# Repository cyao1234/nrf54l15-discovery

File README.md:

# nRF54L15 Discovery

The nRF54L15 Discovery board is a development kit designed around the nRF54L15 and nRF52820 multiprotocol Bluetooth low-power SoCs. In the normal configuration, the nRF52820 is used as an interface CMSIS-DAP MCU, enabling onboard debugging and programming, eliminating the need for external debuggers. The Interface MCU interfaces with the host via USB and exposes an SWD and UART bridge for development usage.

Both MCUs are connected via two mousebite bridges, which can be snapped in two, allowing both chips to be used separately. Both boards have standalone voltage regulators and have their own USB-C power supply connector.

The processors are paired with an nPM1300 PMIC that supports LiPo charging and a TPS63900 high-efficiency, low Iq buck-boost converter. Both voltage regulators can be configured for 1.8V or 3.3V, enabling a flexible operating voltage domain. The nPM1300 also negotiates USB-C PD with your charger and dynamically changes the battery charging rate.

It also has USB-C, LEDs, Buttons, and U.FL receptacles for a 2.4 GHz Antenna and a 13.56 MHz NFC Antenna. The SWD and UART headers are exposed via I/O pins.

### Key Features
- Nordic Semiconductor [nRF54L15](https://www.nordicsemi.com/Products/nRF54L15) SoC
    - 128 MHz Arm Cortex®-M33 processor and 128 MHz RISC-V coprocessor 
    - 1.5 MB NVM and 256 KB RAM
    - Multiprotocol 2.4 GHz radio supporting Bluetooth Low Energy, 802.15.4-2020, and 2.4 GHz proprietary modes (up to 4 Mbps)
    - Advanced security features with physical protection
    - Global RTC (GRTC) available in System OFF mode
    - 5x SPI/UART/I2C, 3x PWM, 2x QDEC, I2S, PDM, 14-bit ADC, GPIOs
    - Integrated NFC-A Tag
    - 0.7 μA to 2.9 μA sleep mode power consumption
    - U.FL NFC connector
- Nordic Semiconductor [nRF52820](https://www.nordicsemi.com/Products/nRF52820) SoC
    - 64 MHz Arm Cortex®-M4
    - 256 KB Flash and 32 KB RAM
    - Full Speed USB 2.0
    - Bluetooth Low Energy multiprotocol
    - U.FL 2.4GHz NFC Antenna
- [nPM1300](https://www.nordicsemi.com/Products/nPM1300) 500 nA PMIC with integrated 32-800mA LiPo battery charger
    - 200 mA buck-boost converter with 93% efficiency
    - 50 mA switchable LDO for LEDs (turn off for 0 current leakage)
    - 1.0-3.3V variable voltage configurable in 100 mV steps
    - 32-800 mA LiPo battery charger with power path
    - USB Type-C compliant with 100 mA, 500 mA, and 1500 mA current limit
- Up to 48 GPIOs (29 for nRF54L15, 15 for nRF52820, 2 for nPM1300)
- Shipped with CMSIS-DAP pre-flashed on the nRF52820, ready for direct use
- ARM Serial Wire Debug (SWD) port via edge pins and 3-pin header
- TPS63900 75 nA buck-boost converter with 1.8V/3.3V configurable power supply for I/Os
- USB-C, user LED and buttons
- Dual-row 40+20 pins in 91x21mm form factor with castellated edges
- Snappable into 2 individual devboards, all capable of standalone operations
- Supports Zephyr, nRF Connect SDK, Python, etc.

### Hardware Diagram

The hardware design files are also available on [GitHub](https://github.com/cheyao/nrf54l15-discovery/), licensed under the CERN OHL V2.

### Programming guide

The board is programmable out of the box. Just run `west flash -r pyocd` to flash the board.

To get started, just follow Zephyr's [Getting Started](https://docs.zephyrproject.org/latest/develop/getting_started/index.html) guide. Everything is the same, except replace `<your-board-name>` with `nrf54l15_discovery/nrf54l15/cpuapp/s` (or without the `/ns` for secure version).

### Where to Buy

The nRF54L15 Discovery is available on the following sites:

(Got some extra units; cost covers material costs)

| Item | Price |
| --- | ---- |
| PCB | $120 |
| PCBA | $230 |

Download firmware here:
https://github.com/cheyao/nrf54l15-discovery/releases/tag/v1.0

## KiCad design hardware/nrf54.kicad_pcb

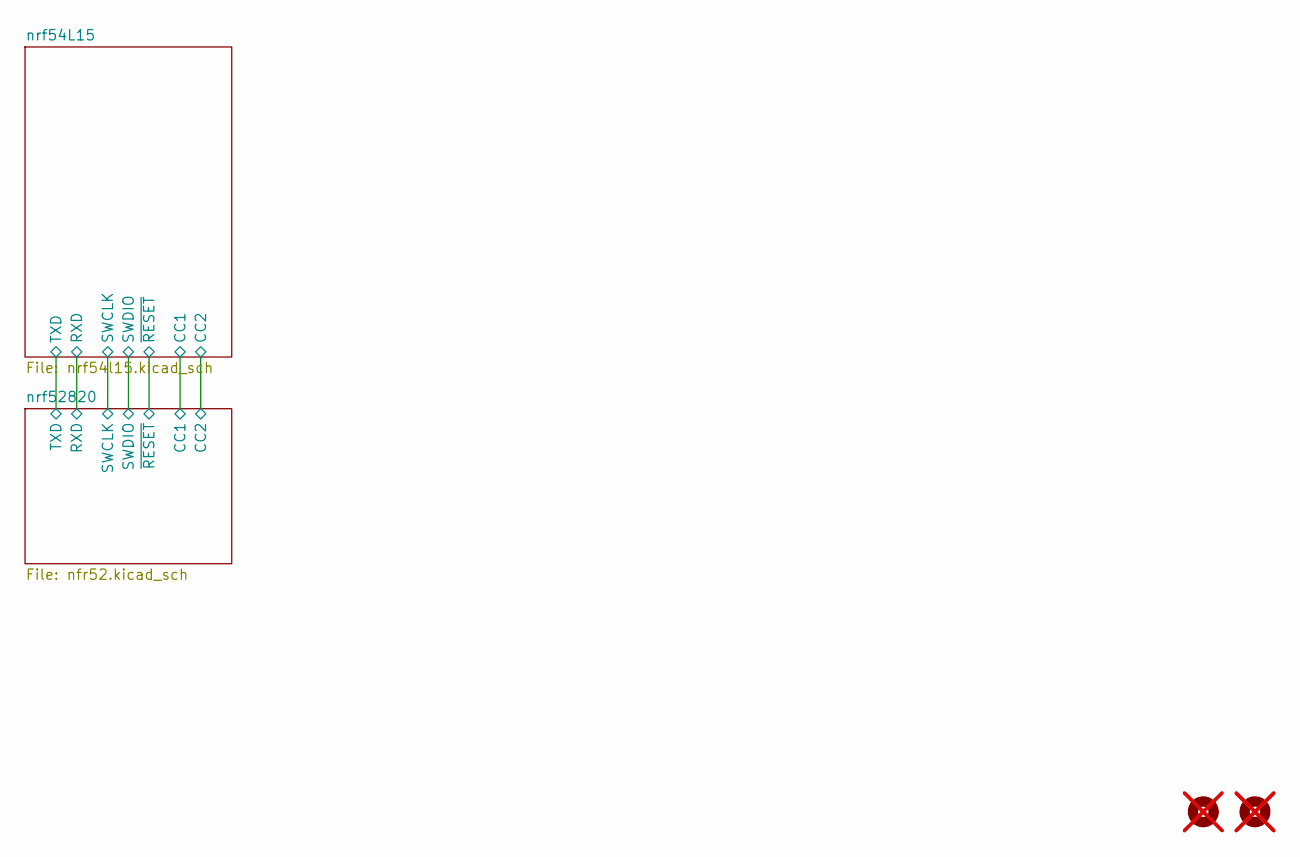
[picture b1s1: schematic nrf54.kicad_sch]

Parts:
H3, H4: MountingHole; MouseBite-Slot_2.0x2.0mm_outset_D0.5mm_P0.85mm_2h_Trace; not fitted

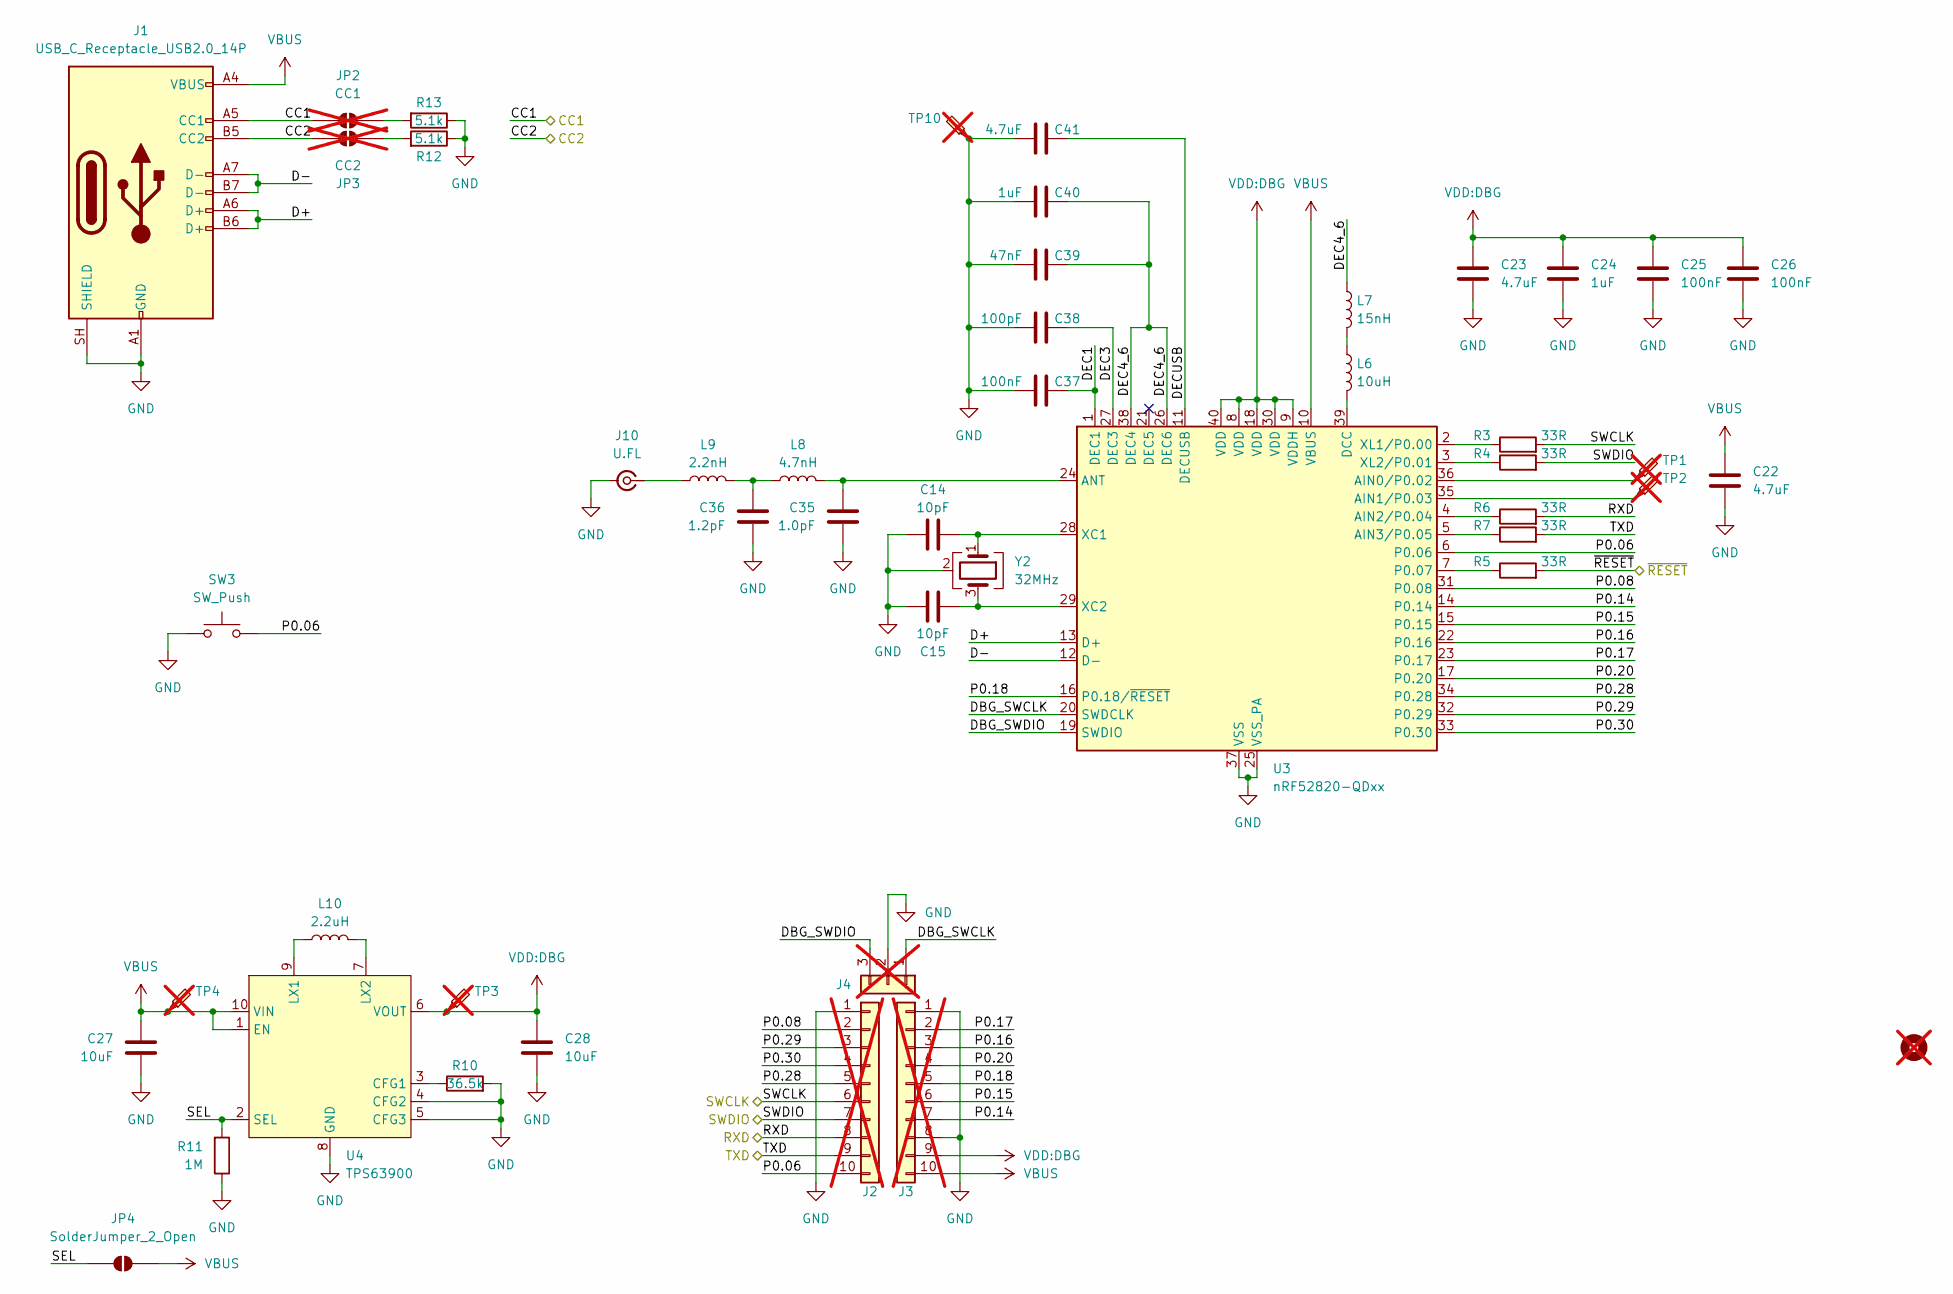
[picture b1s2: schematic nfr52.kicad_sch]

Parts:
C14, C15: 10pF; C_0402_1005Metric; LCSC Part # C106199
C22, C23, C41: 4.7uF; C_0603_1608Metric; LCSC Part # C380302
C24, C40: 1uF; C_0603_1608Metric; LCSC Part # C519560
C25, C26, C37: 100nF; C_0402_1005Metric; LCSC Part # C60474
C27, C28: 10uF; C_0603_1608Metric; LCSC Part # C7432767
C35: 1.0pF; C_0201_0603Metric; LCSC Part # C85893
C36: 1.2pF; C_0201_0603Metric; LCSC Part # C22374839
C38: 100pF; C_0402_1005Metric; LCSC Part # C541383
C39: 47nF; C_0402_1005Metric; LCSC Part # C272875
H1: MountingHole; Icy Electronics Logo; not fitted
J1: USB_C_Receptacle_USB2.0_14P; USB_C_Receptacle_HRO_TYPE-C-31-M-12; LCSC Part # C2681555
J2, J3: Conn_01x10; Castellated_1x10_P2.54mm_Vertical; not fitted
J4: Conn_01x03; PinHeader_1x03_P2.54mm_Vertical; not fitted
J10: U.FL; U.FL_Hirose_U.FL-R-SMT-1_Vertical; LCSC Part # C88374
JP2: CC1; SolderJumper-2_Open_Pad_Small; not fitted
JP3: CC2; SolderJumper-2_Open_Pad_Small; not fitted
JP4: SolderJumper_2_Open; SolderJumper-2_Open_Pad_Small
L6: 10uH; L_0603_1608Metric; LCSC Part # C281107
L7: 15nH; L_0402_1005Metric; LCSC Part # C86059
L8: 4.7nH; L_0201_0603Metric; LCSC Part # C86126
L9: 2.2nH; L_0201_0603Metric; LCSC Part # C98041
L10: 2.2uH; L_1008_2520Metric; LCSC Part # C5832372
R3, R4, R5, R6, R7: 33R; R_0402_1005Metric; LCSC Part # C2906931
R10: 36.5k; R_0402_1005Metric; LCSC Part # C49010116
R11: 1M; R_0402_1005Metric; LCSC Part # C2906900
R12, R13: 5.1k; R_0402_1005Metric; LCSC Part # C852856
SW3: SW_Push; SW_Push_SPST_TSA016; LCSC Part # C2888428
TP1, TP2, TP3, TP4, TP10: TestPoint_Probe; TestPoint_Pad_D1.0mm; not fitted
U3: nRF52820-QDxx; QFN-40-1EP_5x5mm_P0.4mm_EP3.6x3.6mm_ThermalVias
U4: TPS63900; WSON-10-1EP_2.5x2.5mm_P0.5mm_EP1.2x2mm_ThermalVias; LCSC Part # C1518762
Y2: 32MHz; Crystal_SMD_2016-4Pin_2.0x1.6mm; LCSC Part # C5339095

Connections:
/nrf52820/CC1: J1.A5 (CC1), JP2.1 (A); also elsewhere on the board
/nrf52820/CC2: J1.B5 (CC2), JP3.1 (A); also elsewhere on the board
/nrf52820/D+: J1.A6 (D+), J1.B6 (D+), U3.13 (D+)
/nrf52820/D-: J1.A7 (D-), J1.B7 (D-), U3.12 (D-)
/nrf52820/DBG_SWCLK: J4.1, U3.20 (SWDCLK)
/nrf52820/DBG_SWDIO: J4.3, U3.19 (SWDIO)
/nrf52820/DEC1: C37.2, U3.1 (DEC1)
/nrf52820/DEC3: C38.2, U3.27 (DEC3)
/nrf52820/DEC4_6: C39.2, C40.2, L7.1, U3.26 (DEC6), U3.38 (DEC4)
/nrf52820/DECUSB: C41.2, U3.11 (DECUSB)
/nrf52820/P0.06: J2.10, SW3.1, U3.6 (P0.06)
/nrf52820/P0.08: J2.2, U3.31 (P0.08)
/nrf52820/P0.14: J3.7, U3.14 (P0.14)
/nrf52820/P0.15: J3.6, U3.15 (P0.15)
/nrf52820/P0.16: J3.3, U3.22 (P0.16)
/nrf52820/P0.17: J3.2, U3.23 (P0.17)
/nrf52820/P0.18: J3.5, U3.16 (P0.18/~RESET)
/nrf52820/P0.20: J3.4, U3.17 (P0.20)
/nrf52820/P0.28: J2.5, U3.34 (P0.28)
/nrf52820/P0.29: J2.3, U3.32 (P0.29)
/nrf52820/P0.30: J2.4, U3.33 (P0.30)
/nrf52820/RXD: J2.8, R6.2; also elsewhere on the board
/nrf52820/SEL: JP4.1 (A), R11.2, U4.2 (SEL)
/nrf52820/SWCLK: J2.6, R3.2; also elsewhere on the board
/nrf52820/SWDIO: J2.7, R4.2; also elsewhere on the board
/nrf52820/TXD: J2.9, R7.2; also elsewhere on the board
/nrf52820/~RESET: R5.2; also elsewhere on the board
GND: C14.1, C15.1, C22.2, C23.2, C24.2, C25.2, C26.2, C27.2, C28.2, C35.2, C36.2, C37.1, C38.1, C39.1, C40.1, C41.1, J1.A1 (GND), J1.A12 (GND), J1.B1 (GND), J1.B12 (GND), J1.SH (SHIELD), J2.1, J3.1, J3.8, J4.2, J10.2 (Ext), R10.2, R11.1, R12.1, R13.1, SW3.2, TP10.1 (1_1), U3.25 (VSS_PA), U3.37 (VSS), U3.41 (VSS), U4.4 (CFG2), U4.5 (CFG3), U4.8 (GND), U4.11 (GND), Y2.2 (G), Y2.4 (G); also elsewhere on the board
unnamed: C36.1, L8.1, L9.2
unnamed: J10.1 (In), L9.1
unnamed: JP2.2 (B), R13.2
unnamed: JP3.2 (B), R12.2
unnamed: L6.1, L7.2
unnamed: TP1.1 (1_1), U3.36 (AIN0/P0.02)
unnamed: TP2.1 (1_1), U3.35 (AIN1/P0.03)
unnamed: R6.1, U3.4 (AIN2/P0.04)
unnamed: R7.1, U3.5 (AIN3/P0.05)
unnamed: C35.1, L8.2, U3.24 (ANT)
unnamed: L6.2, U3.39 (DCC)
unnamed: R5.1, U3.7 (P0.07)
unnamed: C14.2, U3.28 (XC1), Y2.1
unnamed: C15.2, U3.29 (XC2), Y2.3
unnamed: R3.1, U3.2 (XL1/P0.00)
unnamed: R4.1, U3.3 (XL2/P0.01)
unnamed: R10.1, U4.3 (CFG1)
unnamed: L10.1, U4.9 (LX1)
unnamed: L10.2, U4.7 (LX2)
VBUS: C22.1, C27.1, J1.A4 (VBUS), J1.A9 (VBUS), J1.B4 (VBUS), J1.B9 (VBUS), J3.10, JP4.2 (B), TP4.1 (1_1), U3.10 (VBUS), U4.1 (EN), U4.10 (VIN); also elsewhere on the board
VDD:DBG: C23.1, C24.1, C25.1, C26.1, C28.1, J3.9, TP3.1 (1_1), U3.8 (VDD), U3.9 (VDDH), U3.18 (VDD), U3.30 (VDD), U3.40 (VDD), U4.6 (VOUT)

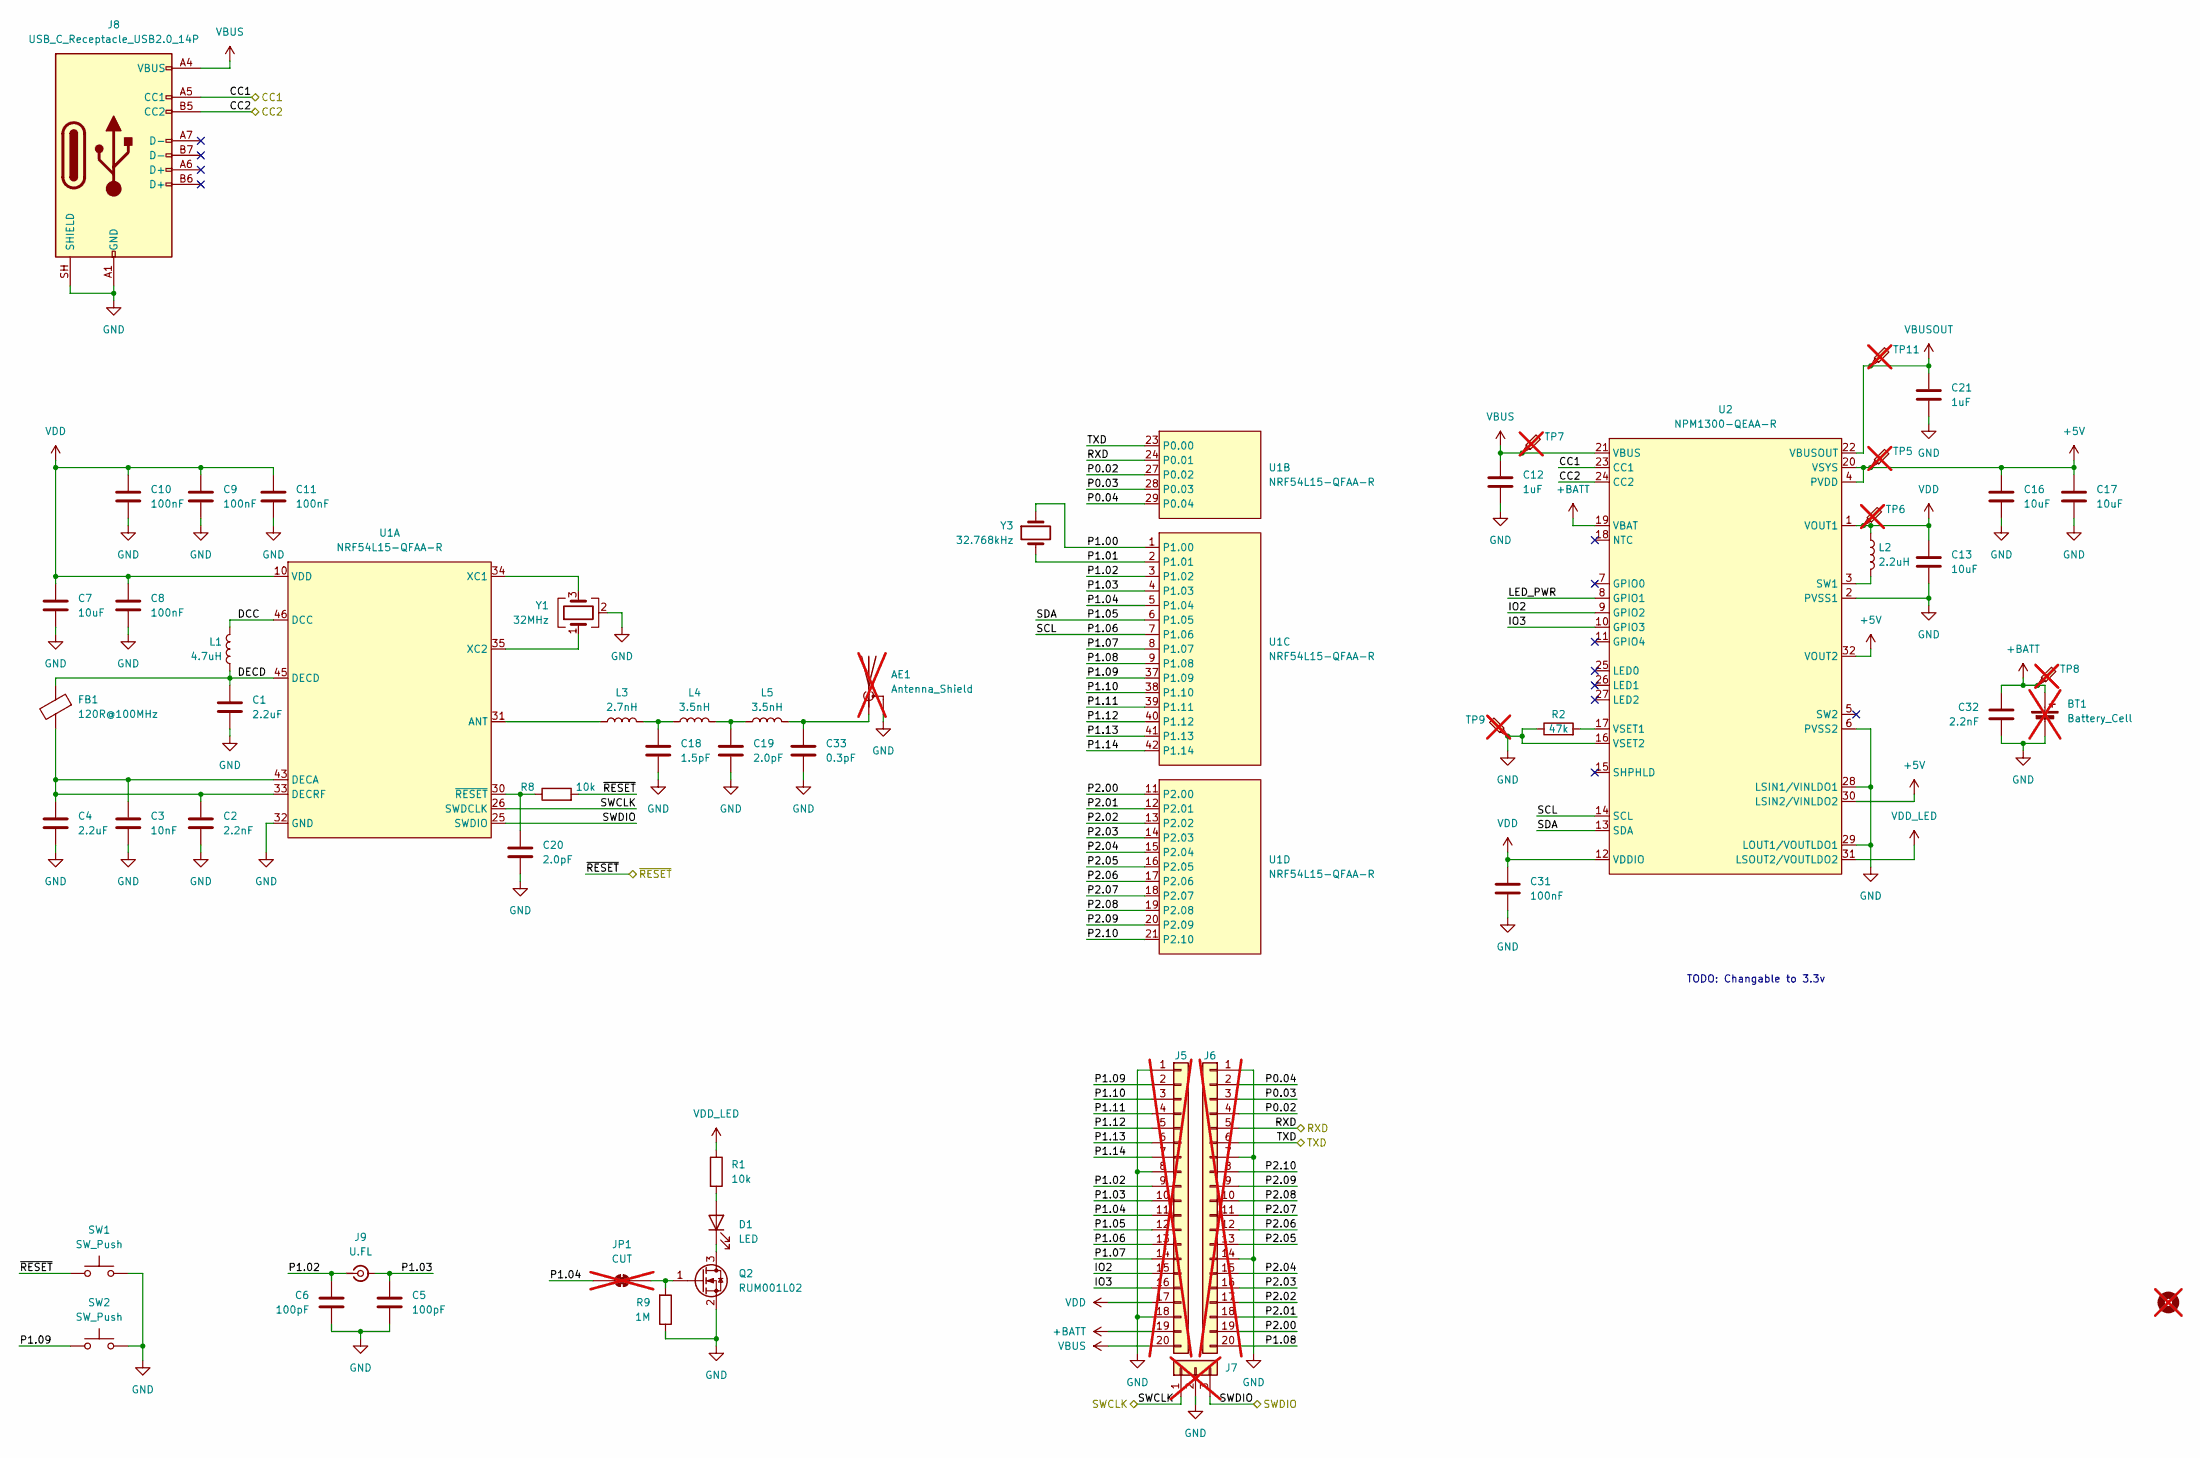
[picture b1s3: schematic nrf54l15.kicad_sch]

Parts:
AE1: Antenna_Shield; Texas_SWRA117D_2.4GHz_Right; not fitted
BT1: Battery_Cell; not fitted
C1, C4: 2.2uF; C_0402_1005Metric; LCSC Part # C723363
C2, C32: 2.2nF; C_0402_1005Metric; LCSC Part # C106861
C3: 10nF; C_0402_1005Metric; LCSC Part # C5137480
C5, C6: 100pF; C_0402_1005Metric; LCSC Part # C541383
C7, C13, C16, C17: 10uF; C_0603_1608Metric; LCSC Part # C7432767
C8, C9, C10, C11, C31: 100nF; C_0402_1005Metric; LCSC Part # C60474
C12, C21: 1uF; C_0603_1608Metric; LCSC Part # C519560
C18: 1.5pF; C_0201_0603Metric; LCSC Part # C435397
C19: 2.0pF; C_0201_0603Metric; LCSC Part # C22374842
C20: 2.0pF; C_0402_1005Metric; LCSC Part # C281756
C33: 0.3pF; C_0201_0603Metric; LCSC Part # C723329
D1: LED; LED_0402_1005Metric; LCSC Part # C51933306
FB1: 120R@100MHz; L_0402_1005Metric; LCSC Part # C141722
H2: MountingHole; Icy Electronics Logo; not fitted
J5, J6: Conn_01x20; Castellated_1x20_P2.54mm_Vertical; not fitted
J7: Conn_01x03; PinHeader_1x03_P2.54mm_Vertical; not fitted
J8: USB_C_Receptacle_USB2.0_14P; USB_C_Receptacle_HRO_TYPE-C-31-M-12; LCSC Part # C2681555
J9: U.FL; U.FL_Hirose_U.FL-R-SMT-1_Vertical; LCSC Part # C88374
JP1: CUT; SolderJumper-2_Bridged_Pad_Small; not fitted
L1: 4.7uH; L_0603_1608Metric; LCSC Part # C394952
L2: 2.2uH; L_1008_2520Metric; LCSC Part # C5832372
L3: 2.7nH; L_0201_0603Metric; LCSC Part # C337946
L4, L5: 3.5nH; L_0201_0603Metric; LCSC Part # C3911055
Q2: RUM001L02; SOT-723; LCSC Part # C42412321
R1, R8: 10k; R_0402_1005Metric; LCSC Part # C2906861
R2: 47k; R_0402_1005Metric; LCSC Part # C163830
R9: 1M; R_0402_1005Metric; LCSC Part # C2906900
SW1, SW2: SW_Push; SW_Push_SPST_TSA016; LCSC Part # C2888428
TP5, TP6, TP7, TP8, TP9, TP11: TestPoint_Probe; TestPoint_Pad_D1.0mm; not fitted
U1: NRF54L15-QFAA-R; QFN-48-1EP_6x6mm_P0.4mm_EP4.6x4.6mm_ThermalVias
U2: NPM1300-QEAA-R; VQFN-32-1EP_5x5mm_P0.5mm_EP3.5x3.5mm_ThermalVias
Y1: 32MHz; Crystal_SMD_2016-4Pin_2.0x1.6mm; LCSC Part # C5339095
Y3: 32.768kHz; Crystal_SMD_2012-2Pin_2.0x1.2mm; LCSC Part # C99009

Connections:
+5V: C16.1, C17.1, TP5.1 (1_1), U2.4 (PVDD), U2.20 (VSYS), U2.30 (LSIN2/VINLDO2), U2.32 (VOUT2)
+BATT: BT1.1 (+), C32.1, J5.19, TP8.1 (1_1), U2.19 (VBAT)
/nrf54L15/DCC: L1.2, U1.46 (DCC)
/nrf54L15/DECD: C1.1, FB1.1, L1.1, U1.45 (DECD)
/nrf54L15/IO2: J5.15, U2.9 (GPIO2)
/nrf54L15/IO3: J5.16, U2.10 (GPIO3)
/nrf54L15/LED_PWR: U2.8 (GPIO1)
/nrf54L15/P0.02: J6.4, U1.27 (P0.02)
/nrf54L15/P0.03: J6.3, U1.28 (P0.03)
/nrf54L15/P0.04: J6.2, U1.29 (P0.04)
/nrf54L15/P1.00: U1.1 (P1.00), Y3.1
/nrf54L15/P1.01: U1.2 (P1.01), Y3.2
/nrf54L15/P1.02: C6.1, J5.9, J9.1 (In), U1.3 (P1.02)
/nrf54L15/P1.03: C5.1, J5.10, J9.2 (Ext), U1.4 (P1.03)
/nrf54L15/P1.04: J5.11, JP1.1 (A), U1.5 (P1.04)
/nrf54L15/P1.05: J5.12, U1.6 (P1.05), U2.13 (SDA)
/nrf54L15/P1.06: J5.13, U1.7 (P1.06), U2.14 (SCL)
/nrf54L15/P1.07: J5.14, U1.8 (P1.07)
/nrf54L15/P1.08: J6.20, U1.9 (P1.08)
/nrf54L15/P1.09: J5.2, SW2.1, U1.37 (P1.09)
/nrf54L15/P1.10: J5.3, U1.38 (P1.10)
/nrf54L15/P1.11: J5.4, U1.39 (P1.11)
/nrf54L15/P1.12: J5.5, U1.40 (P1.12)
/nrf54L15/P1.13: J5.6, U1.41 (P1.13)
/nrf54L15/P1.14: J5.7, U1.42 (P1.14)
/nrf54L15/P2.00: J6.19, U1.11 (P2.00)
/nrf54L15/P2.01: J6.18, U1.12 (P2.01)
/nrf54L15/P2.02: J6.17, U1.13 (P2.02)
/nrf54L15/P2.03: J6.16, U1.14 (P2.03)
/nrf54L15/P2.04: J6.15, U1.15 (P2.04)
/nrf54L15/P2.05: J6.13, U1.16 (P2.05)
/nrf54L15/P2.06: J6.12, U1.17 (P2.06)
/nrf54L15/P2.07: J6.11, U1.18 (P2.07)
/nrf54L15/P2.08: J6.10, U1.19 (P2.08)
/nrf54L15/P2.09: J6.9, U1.20 (P2.09)
/nrf54L15/P2.10: J6.8, U1.21 (P2.10)
/nrf52820/CC1: J8.A5 (CC1), U2.23 (CC1); also elsewhere on the board
/nrf52820/CC2: J8.B5 (CC2), U2.24 (CC2); also elsewhere on the board
/nrf52820/RXD: J6.5, U1.24 (P0.01); also elsewhere on the board
/nrf52820/SWCLK: J7.1, U1.26 (SWDCLK); also elsewhere on the board
/nrf52820/SWDIO: J7.3, U1.25 (SWDIO); also elsewhere on the board
/nrf52820/TXD: J6.6, U1.23 (P0.00); also elsewhere on the board
/nrf52820/~RESET: R8.2, SW1.1; also elsewhere on the board
GND: AE1.2 (Shield), BT1.2 (-), C1.2, C2.2, C3.2, C4.2, C5.2, C6.2, C7.2, C8.2, C9.2, C10.2, C11.2, C12.2, C13.2, C16.2, C17.2, C18.2, C19.2, C20.2, C21.2, C31.2, C32.2, C33.2, J5.1, J5.8, J5.18, J6.1, J6.7, J6.14, J7.2, J8.A1 (GND), J8.A12 (GND), J8.B1 (GND), J8.B12 (GND), J8.SH (SHIELD), Q2.2 (S), R2.1, R9.1, SW1.2, SW2.2, TP9.1 (1_1), U1.32 (GND), U1.44 (GND), U1.49 (GND), U2.2 (PVSS1), U2.6 (PVSS2), U2.16 (VSET2), U2.28 (LSIN1/VINLDO1), U2.29 (LOUT1/VOUTLDO1), U2.33 (GND), Y1.2 (G), Y1.4 (G); also elsewhere on the board
unnamed: AE1.1 (A), C33.1, L5.2
unnamed: C18.1, L3.2, L4.1
unnamed: C19.1, L4.2, L5.1
unnamed: D1.2 (A), R1.2
unnamed: D1.1 (K), Q2.3 (D)
unnamed: JP1.2 (B), Q2.1 (G), R9.2
unnamed: L3.1, U1.31 (ANT)
unnamed: C2.1, C3.1, C4.1, FB1.2, U1.33 (DECRF), U1.43 (DECA)
unnamed: U1.34 (XC1), Y1.3
unnamed: U1.35 (XC2), Y1.1
unnamed: C20.1, R8.1, U1.30 (~RESET)
unnamed: L2.2, U2.3 (SW1)
unnamed: R2.2, U2.17 (VSET1)
VBUS: C12.1, J5.20, J8.A4 (VBUS), J8.A9 (VBUS), J8.B4 (VBUS), J8.B9 (VBUS), TP7.1 (1_1), U2.21 (VBUS); also elsewhere on the board
VBUSOUT: C21.1, TP11.1 (1_1), U2.22 (VBUSOUT)
VDD: C7.1, C8.1, C9.1, C10.1, C11.1, C13.1, C31.1, J5.17, L2.1, TP6.1 (1_1), U1.10 (VDD), U1.22 (VDD), U1.36 (VDD), U1.47 (VDD), U1.48 (VDD), U2.1 (VOUT1), U2.12 (VDDIO)
VDD_LED: R1.1, U2.31 (LSOUT2/VOUTLDO2)

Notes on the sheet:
TODO: Changable to 3.3v

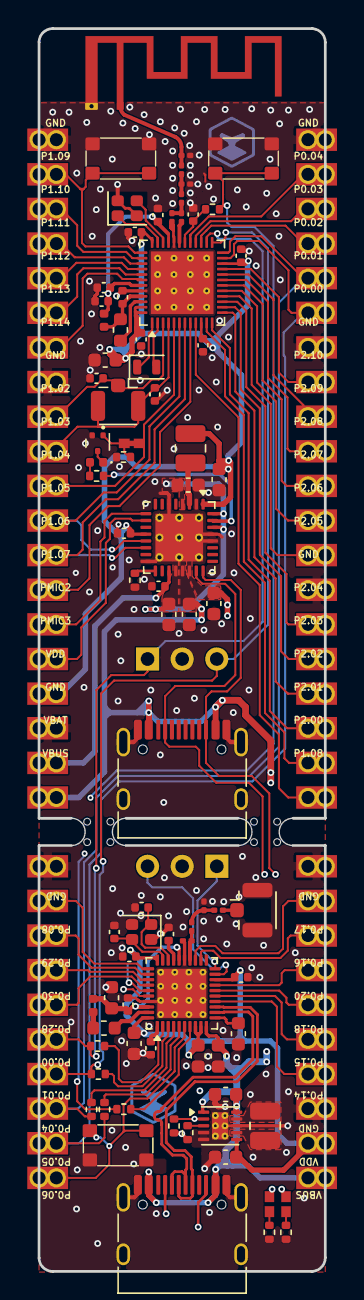
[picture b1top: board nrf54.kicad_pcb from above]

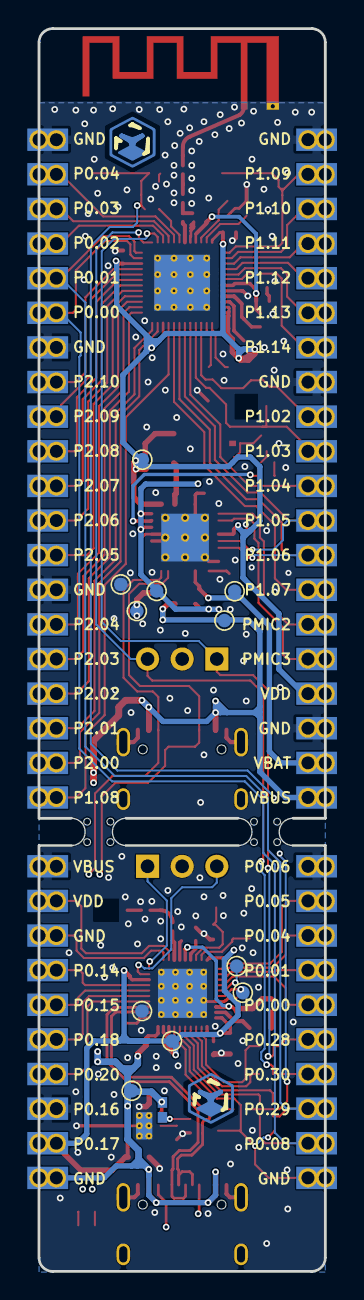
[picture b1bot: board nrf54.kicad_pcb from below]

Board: 4 copper layers, 21.0 x 91.2 mm, 104 parts (18 on the bottom side), 100 nets.

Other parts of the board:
H2#2: MountingHole; Icy Electronics Logo

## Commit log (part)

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2026-06-15 Init
